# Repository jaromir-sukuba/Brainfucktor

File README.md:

Aim of this still unfinished project is to make functional Brainfuck computer in less than 1kB of code, as expected from 1kB challenge on hackaday.io - https://hackaday.io/contest/18215-the-1kb-challenge
Project page of this project is here - https://hackaday.io/project/18445-brainfcktor

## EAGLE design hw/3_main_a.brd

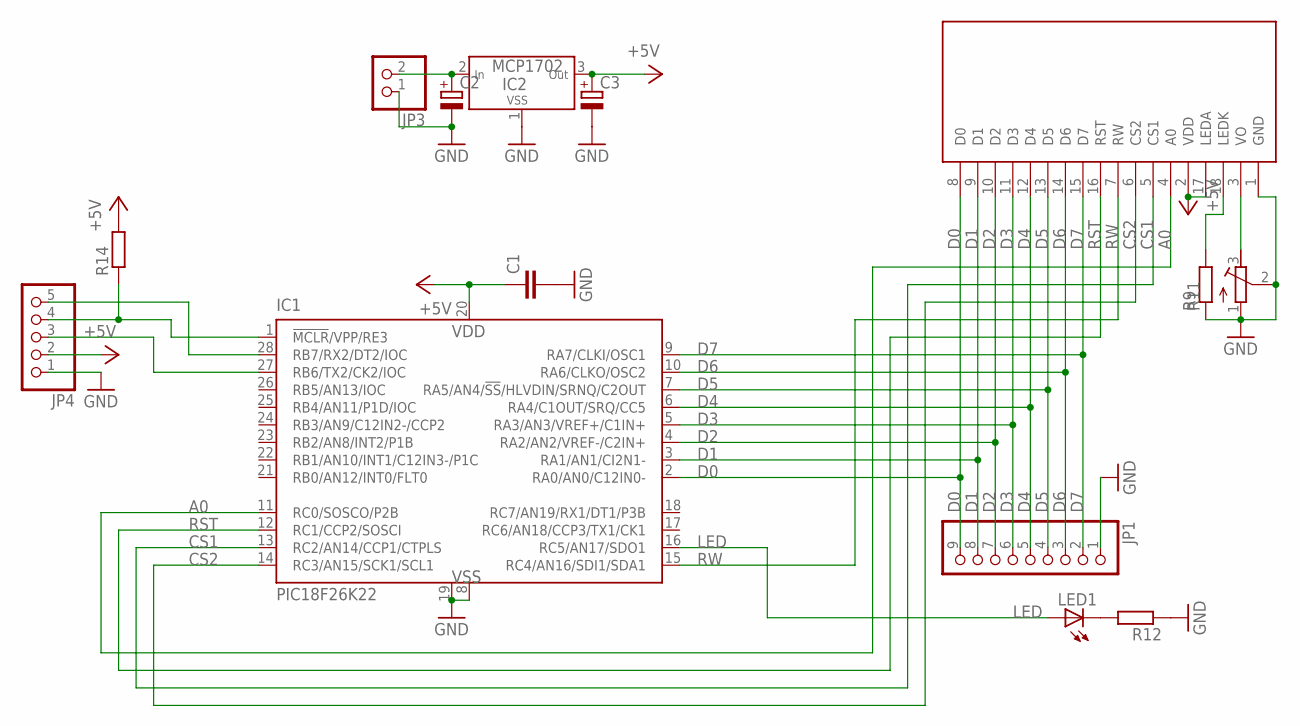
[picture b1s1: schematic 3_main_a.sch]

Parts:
C1: C-EU025-025X050; C025-025X050
C2, C3: CPOL-EUE2-4; E2-4
IC1: PIC18F26K22; DIL28-3
IC2: MCP1702; TO-92
JP1: PINHD-1X09_2.54-90°; 1X09/90
JP3: PINHD-1X2; 1X02
JP4: PINHD-1X05_2.54-90°; 1X05/90
LCD1: DEM122032
LED1: LED3MM
R9, R12, R14: R_0207; R_0207_BIGPADS
R11: R-TRIMM3339P; RTRIM3339P

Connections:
+5V: C1.1, C3.+, IC1.20 (VDD), IC2.3 (OUT), JP4.2, LCD1.2 (VDD), LCD1.17 (LEDA), R14.P$2 (2)
A0: IC1.11 (RC0/SOSCO/P2B), LCD1.4 (A0)
CS1: IC1.13 (RC2/AN14/CCP1/CTPLS), LCD1.5 (CS1)
CS2: IC1.14 (RC3/AN15/SCK1/SCL1), LCD1.6 (CS2)
D0: IC1.2 (RA0/AN0/C12IN0-), JP1.9, LCD1.8 (D0)
D1: IC1.3 (RA1/AN1/CI2N1-), JP1.8, LCD1.9 (D1)
D2: IC1.4 (RA2/AN2/VREF-/C2IN+), JP1.7, LCD1.10 (D2)
D3: IC1.5 (RA3/AN3/VREF+/C1IN+), JP1.6, LCD1.11 (D3)
D4: IC1.6 (RA4/C1OUT/SRQ/CC5), JP1.5, LCD1.12 (D4)
D5: IC1.7 (RA5/AN4/!SS!/HLVDIN/SRNQ/C2OUT), JP1.4, LCD1.13 (D5)
D6: IC1.10 (RA6/CLKO/OSC2), JP1.3, LCD1.14 (D6)
D7: IC1.9 (RA7/CLKI/OSC1), JP1.2, LCD1.15 (D7)
GND: C1.2, C2.-, C3.-, IC1.8 (VSS), IC1.19 (VSS), IC2.1 (VSS), JP1.1, JP3.1, JP4.1, LCD1.1 (GND), R9.P$1 (1), R11.1 (E), R11.2 (S), R12.P$1 (1)
LED: IC1.16 (RC5/AN17/SDO1), LED1.A
unnamed: LCD1.18 (LEDK), R9.P$2 (2)
unnamed: LCD1.3 (VO), R11.3 (A)
unnamed: LED1.K (C), R12.P$2 (2)
unnamed: C2.+, IC2.2 (IN), JP3.2
unnamed: IC1.1 (!MCLR!/VPP/RE3), JP4.4, R14.P$1 (1)
unnamed: IC1.28 (RB7/RX2/DT2/IOC), JP4.5
unnamed: IC1.27 (RB6/TX2/CK2/IOC), JP4.3
RST: IC1.12 (RC1/CCP2/SOSCI), LCD1.16 (RST)
RW: IC1.15 (RC4/AN16/SDI1/SDA1), LCD1.7 (RW)

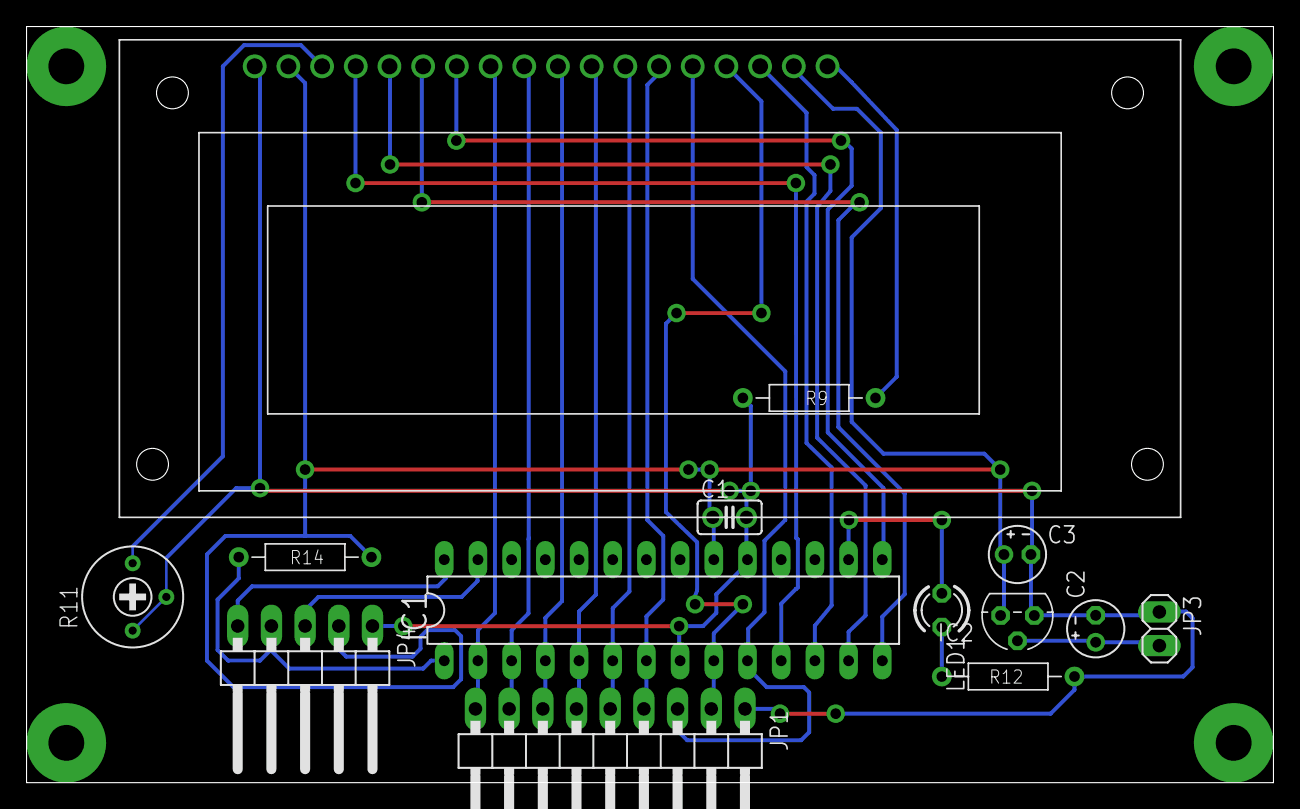
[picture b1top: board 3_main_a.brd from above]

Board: 2 copper layers, 94.0 x 57.0 mm, 14 parts (0 on the bottom side), 23 nets.

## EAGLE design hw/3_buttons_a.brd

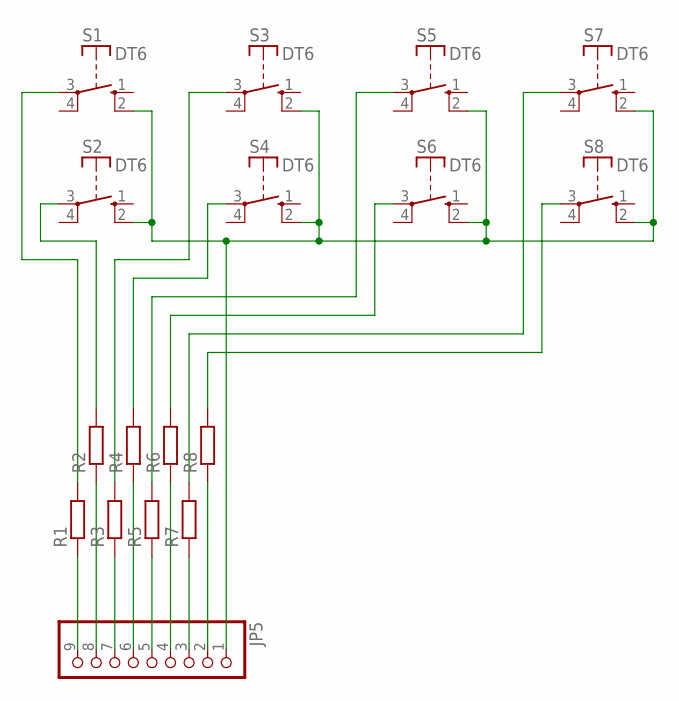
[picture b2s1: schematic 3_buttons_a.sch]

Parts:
JP5: PINHD-1X09_2.54-90°; 1X09/90
R1, R2, R3, R4, R5, R6, R7, R8: R_0207; R_0207_BIGPADS
S1, S2, S3, S4, S5, S6, S7, S8: DT6

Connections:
unnamed: JP5.9, R1.P$1 (1)
unnamed: JP5.8, R2.P$1 (1)
unnamed: JP5.7, R3.P$1 (1)
unnamed: JP5.6, R4.P$1 (1)
unnamed: JP5.5, R5.P$1 (1)
unnamed: JP5.4, R6.P$1 (1)
unnamed: JP5.3, R7.P$1 (1)
unnamed: JP5.2, R8.P$1 (1)
unnamed: JP5.1, S1.2 (S), S2.2 (S), S3.2 (S), S4.2 (S), S5.2 (S), S6.2 (S), S7.2 (S), S8.2 (S)
unnamed: R1.P$2 (2), S1.3
unnamed: R2.P$2 (2), S2.3
unnamed: R3.P$2 (2), S3.3
unnamed: R4.P$2 (2), S4.3
unnamed: R5.P$2 (2), S5.3
unnamed: R6.P$2 (2), S6.3
unnamed: R7.P$2 (2), S7.3
unnamed: R8.P$2 (2), S8.3

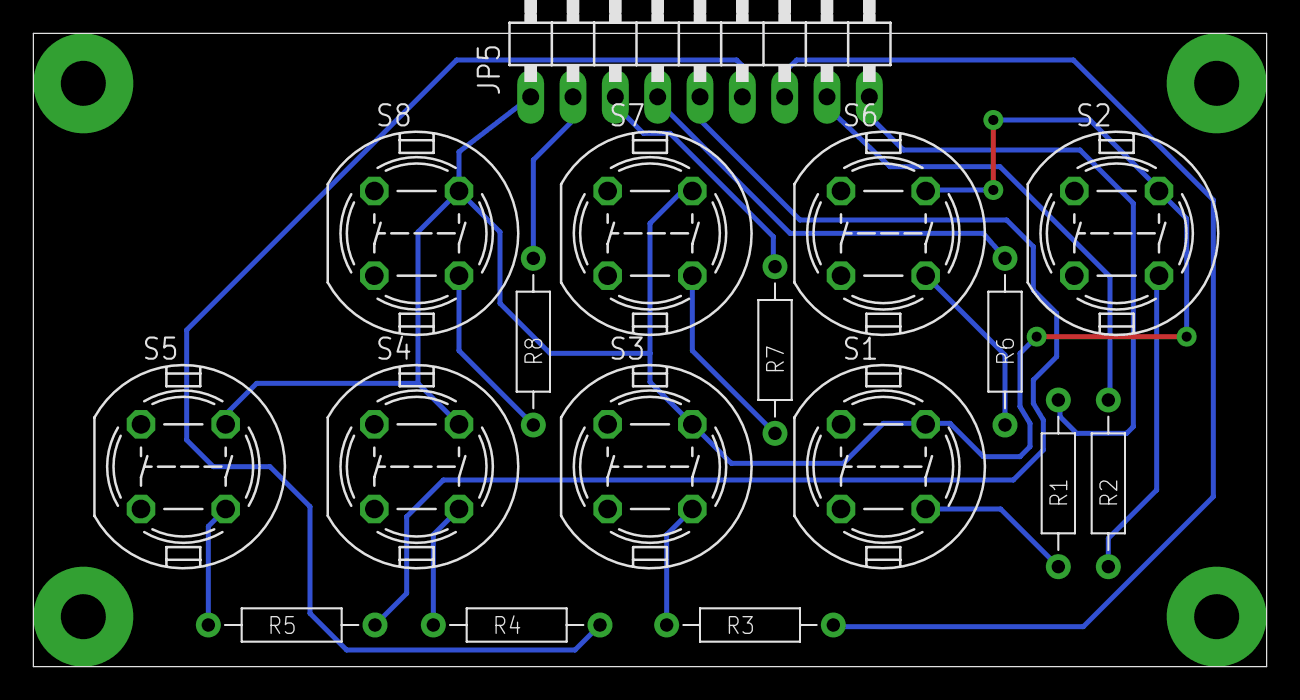
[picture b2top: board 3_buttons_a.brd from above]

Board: 2 copper layers, 74.0 x 38.0 mm, 17 parts (0 on the bottom side), 17 nets.

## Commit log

2016-12-01 :boom::camel: Added .gitattributes
2016-12-01 first try
2016-12-01 readme updated
2016-12-27 graphic LCD support
2017-01-04 almost final release
2017-01-04 minor updates
